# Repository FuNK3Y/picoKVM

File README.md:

# PicoKVM
An inexpensive network KVM that can switch USB and monitor inputs simultaneously

## Why
Samsung makes great monitors, but they often lack a KVM. The project started as a way to switch them along with the USB devices, over their network API. It was later generalized to most monitors, driven over HDMI DDC/CI by its own board, while still driving network-controlled monitors and devices.

## Features
- Switches the USB devices and the monitors' inputs together
- Drives most monitors over HDMI DDC/CI, and others (or any device: a lamp, ...) over the network
- No video goes through it: every computer is connected directly to every monitor, so HDCP, VRR, G-Sync, FreeSync, HDR, ... work natively
- Controlled from its button, a web page or an HTTP API, from any device on the network

## Hardware
picoKVM runs on its own board, designed in [`hardware/`](hardware/README.md): an ESP32-S3, a USB 3.0 switch (two computers, one peripheral port), two HDMI ports carrying DDC/CI only (no video) to switch monitor inputs, an RGB status LED, and a Grove port for an [M5Stack key unit](https://shop.m5stack.com/products/mechanical-key-button-unit) as the switch button.

The original build (M5Stack AtomS3 Lite + USB multiplexer) is no longer supported; its last version is [5d5997c](https://github.com/FuNK3Y/picoKVM/tree/5d5997c).

## Install
1. Open the **[browser installer](https://funk3y.github.io/picoKVM/)** in Chrome or Edge, and plug the board's AUX / FLASH USB-C port into the computer.
2. Install, then connect the board to your Wi-Fi from the same page.
3. *Visit device* opens the [settings page](#settings): set the [admin password](#admin-password) first, then the input names and the monitors.

## Wiring
- Computers' video goes directly to the monitors, as without a KVM.
- Each computer's USB goes to the board; the keyboard and mouse go to its peripheral port, through a hub (the monitor's own hub works).
- For monitors driven over DDC/CI, an HDMI cable goes from one of the board's HDMI ports to the monitor. It carries only the input-switch commands, no video. Monitors driven over the network need none.

```mermaid
graph LR
    KB["Keyboard"] <--> |USB| HUB["USB hub"]
    MOUSE["Mouse"] <--> |USB| HUB
    KVM <--> |USB| HUB
    PC1["Computer 1"] --> |Video| MON["Monitor"]
    PC2["Computer 2"] --> |Video| MON
    PC1 <--> |USB| KVM["picoKVM"]
    PC2 <--> |USB| KVM
    KVM -.-> |"HDMI (DDC/CI only)"| MON
    style MON fill:#f9f,stroke:#333
    style KVM fill:#bbf,stroke:#333
    style HUB fill:#ddd,stroke:#333
    style KB fill:#ddd,stroke:#333
    style MOUSE fill:#ddd,stroke:#333
    style PC1 fill:#ddd,stroke:#333
    style PC2 fill:#ddd,stroke:#333
```

## Settings
The settings page (*Settings*, below the switch button at `http://picokvm.local`) edits everything: Wi-Fi, input names and colors, LED brightness, admin password, monitors and [updates](#updates).

### Admin password
Once set, the admin password protects everything the settings page does: opening it, reading and changing the configuration, and installing updates, from the page or through the API. The browser asks for it (any user name); API calls send it as HTTP Basic credentials, e.g. `curl -u admin:<password>`. Switching inputs, the state and `/metrics` stay open.

**Until it is set, all of that is open to anyone on the network.**

To remove it, use *Clear password*, then *Save*, on the settings page, or send `"admin_password": null` to `/api/config`; everything above is then open again.

It travels over plain HTTP, so anyone able to watch the network traffic can read it.

### Monitors
Monitors are added on the settings page: a form for DDC/CI monitors, JSON for the others ([`config.example.json`](config.example.json) has an example of each).

#### DDC/CI monitors
Enable DDC/CI in the monitor's menu. For each computer, choose the monitor input it is on. The settings page reads the monitor: its name, the input it is on now, and the inputs it lists, named as the MCCS standard names them (VCP `0x60`: `15` DisplayPort 1, `17` HDMI 1, ...). Some monitors use other values, or name their ports differently: put the monitor on each computer's input by hand, and the page shows which value it is (*Other value...* takes any number). *Power the monitor on first* wakes up monitors that keep DDC/CI alive in standby.

The monitor must accept DDC/CI on an input that is not the active one, since it is showing the other computer when the command arrives. Most do: tested on **AOC, Samsung, Dell, Acer, Philips and Lenovo** monitors. Some have no DDC/CI at all (the Samsung G80SD): drive those over the network.

#### Samsung monitors over the network
For Samsung smart monitors without DDC/CI, the KVM sends remote-control key presses: enable IP remote on the monitor *(Connection > Network > Expert Settings)*. Find a repeatable sequence of keys that selects each input from the home screen, and write it with the [key codes](https://github.com/ollo69/ha-samsungtv-smart/blob/master/docs/Key_codes.md) as a `SamsungMonitor`. `KEY_RETURN` first also wakes the monitor up; `command_delay` (or a `delay` on one key) slows the sequence down if the menu cannot keep up.

#### Other network devices
A `GenericDevice` sends an HTTP request for each input: another monitor's API (e.g. [SmartThings](https://github.com/ollo69/ha-samsungtv-smart/issues/274#issuecomment-2597627685), untested), a lamp, ...

## Use
Switch with the button, the web page at `http://picokvm.local` (it follows the KVM whoever switches it), or the API:
```sh
curl -X POST http://picokvm.local/api/active_input/A   # or B; without the input, toggles
curl http://picokvm.local/api/active_input             # the state: active input, switching, last error
curl http://picokvm.local/api/events                   # the state as server-sent events, on every change
```
`/api/config` reads (`GET`) and writes (`POST`) the configuration, without the passwords, only `admin_password_set` tells whether one is set ([admin password](#admin-password) required). `/metrics` gives Wi-Fi signal, memory, USB power and version for Prometheus.

`picokvm` is the default hostname; it can be changed in the settings.

## Updates
*Check for updates*, then *Install*, on the settings page installs the latest [release](https://github.com/FuNK3Y/picoKVM/releases) over the network; *Upload* installs a `firmware-ota.bin` of your own. Settings are kept. The first boot of an update is a trial: if the device is not back on Wi-Fi within 2 minutes, it returns to the previous firmware.

The same through the API, with the [admin password](#admin-password):
```sh
curl -u admin:<admin_password> -X POST http://picokvm.local/api/update/latest
curl -u admin:<admin_password> --data-binary @firmware-ota.bin http://picokvm.local/api/update
```

MicroPython does not check GitHub's certificate when downloading a release: the SHA-256 GitHub publishes only guards against a corrupted download.

## ESPHome
The board can also run [ESPHome](https://esphome.io) instead of this firmware, for a native Home Assistant integration (DDC/CI monitors only). Include the [esphome/picokvm.yaml](esphome/picokvm.yaml) package, then name the computers and set the number of monitors:

```yaml
packages:
  picokvm: github://FuNK3Y/picoKVM/esphome/picokvm.yaml@main

substitutions:
  inputs:
    a: Work laptop
    b: Gaming PC
  monitors: 2
```

Each monitor's input values and the LED colors and brightness are then set from Home Assistant. [esphome/example.yaml](esphome/example.yaml) is a complete starting point; it builds, but has not been run on a board yet.

## Development
[`firmware/build.sh`](firmware/build.sh) builds MicroPython with `src/` frozen in, into `firmware/build/` (needs [ESP-IDF](https://docs.espressif.com/projects/esp-idf/en/v5.5.2/esp32s3/get-started/) v5.5.2):
```sh
. $IDF_PATH/export.sh
firmware/build.sh
```
CI runs the same build on pull requests and `main` and keeps the images as an artifact. A `v*` tag publishes a release and the [installer](install/index.html) to GitHub Pages.

The tests run the application on CPython, with stand-ins for the board ([`tests/mocks.py`](tests/mocks.py)); CI requires 95% coverage:
```sh
python3 -m unittest discover -s tests
```

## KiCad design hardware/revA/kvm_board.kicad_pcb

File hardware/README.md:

# picoKVM board — ESP32-S3 USB 3.0 KVM switch with HDMI DDC/CI

Two PCs (USB 3.0 Type-B) share one peripheral port (USB 3.0 Type-A).  An
ESP32-S3 flips the USB path and tells both monitors to change input over
HDMI DDC/CI.  The HDMI ports carry DDC/+5V only — video goes straight
from the PCs to the monitors.  The firmware is the MicroPython code in
`src/`, built into a MicroPython image by `firmware/` (see the main [README](../README.md)).

## Rev A release (ordered 2026-10-03, JLCPCB)

`revA/` holds the board exactly as it was sent to JLCPCB.  Freerouting is not
deterministic, so **`revA/kvm_board.kicad_pcb` is the design of record**: a
fresh `./build.sh` produces an equivalent board, not the same copper.

| file | what |
|---|---|
| `revA/kvm_board.kicad_pcb` / `.kicad_pro` / `.kicad_dru` | routed board (KiCad 10), its net classes and JLC design rules |
| `revA/jlcpcb/gerbers.zip`, `bom.csv`, `cpl.csv` | the files uploaded to JLCPCB (126 × 75 mm customer panel) |
| `revA/schematic_review.html` | readable schematic: every pin, its net and what else is on it |
| `revA/mechanical.txt` | connector, LED and button positions for the enclosure |
| `revA/thermal_justification.md` | proof that every single-spoke GND pad reaches the In1 plane |
| `revA/impedance.txt` | field-solver results for the 90 Ω pairs on JLC04161H-3313 |
| `revA/img/` | renders (top, bottom, iso, panel) and the Grove J8 pinout |

JLC order settings: 4 layers, 1.6 mm, **specified stackup JLC04161H-3313**,
no impedance control (accepted risk for prototypes, see below), 0.3 mm vias,
1 oz outer / 0.5 oz inner, flying-probe test, Standard PCBA top side,
**edge rails added by customer**, confirm production file and parts placement.

To regenerate the order files from the released board without re-routing:

```
mkdir -p out && cp revA/kvm_board.kicad_* out/
./build.sh fab        # panel (hw/panel.py), Gerbers, PTH/NPTH drill, BOM, CPL -> out/jlcpcb/
```

## Build

```
./build.sh          # netlist + ERC, PCB, routing, DRC, renders, JLCPCB files (all in Docker)
./build.sh noroute  # same, stopping at the placed, unrouted board
./build.sh parts    # re-import the LCSC symbols/footprints/3D models
./build.sh shell    # shell inside the toolchain (KiCad 10 + SKiDL + easyeda2kicad)
```

Sources:

| file | what |
|---|---|
| `hw/kvm_board.py` | the schematic, as SKiDL code — edit this, not the netlist |
| `hw/make_pcb.py` | builds the 4-layer `.kicad_pcb`: placement, planes, net classes, JLC rules |
| `hw/route_ss.py` | hand-designed USB 3.0 SuperSpeed pairs (coupled, matched, no vias) |
| `hw/route_usb2.py` | hand-designed USB 2.0 pairs (coupled, matched, symmetric via pairs) |
| `hw/finish.py` | power neck-downs + plane fanout before routing; GND stitching after |
| `hw/route.py` | Freerouting round-trip (Specctra DSN/SES) for everything else |
| `hw/impedance.py` | 2-D field solver for the 90 Ω pairs on the JLC 3313 stackup |
| `hw/make_fab.py` | JLCPCB `bom.csv` / `cpl.csv` (CPL expressed in JLC's own footprint frame) |
| `hw/panel.py` | JLC assembly panel: rails, mouse bites, fiducials, tooling holes |
| `hw/thermal_report.py` | proves every single-spoke GND pad reaches the In1 plane |
| `hw/checks.py` | manufacturing checks beyond DRC, tuned to JLCDFM: vias near pads, SMD near through-hole pads, tracks near mask openings, USB 2 skew (`./build.sh checks`; part of every build) |
| `hw/review.py` | generates `schematic_review.html` |
| `hw/jlcref.py` | fetches JLC's footprints into `hw/lib/jlcref/` (used by `make_fab.py`) |
| `hw/lib/` | LCSC/EasyEDA imports; only the 3D models the board uses are committed (`./build.sh parts` re-fetches the rest, incl. STEP) |

Outputs in `out/`: `kvm_board.kicad_pro/.kicad_pcb` (open in KiCad 10),
`kvm_board.net`, `kvm_board.erc`, `drc.rpt`, `img/`, `jlcpcb/`,
`mechanical.txt` (positions for the case) and **`schematic_review.html`** —
the reviewable schematic: every chip and connector pin with its net and what
else is on it, grouped by function, plus a net index and automatic checks.

## Status

- [x] Circuit complete, ERC clean (0 errors / 0 warnings); D3 pin 3 (DOUT) is
      explicitly marked no-connect (single LED, no chain)
- [x] All parts in JLCPCB/LCSC stock (checked 2026-10-01); passives are basic parts
- [x] Placed and **fully routed**: DRC 0 errors, 0 unconnected.  Board:
      `out/drc.rpt`; JLC panel: `out/drc_panel.rpt`.  `min_resolved_spokes`
      is 1; every pad that would have a single outer-pour spoke is proven to
      reach the In1 GND plane independently in `out/thermal_justification.md`
- [x] 90 Ω pair geometry verified with a 2-D field solver (`hw/impedance.py`, see below)
- [ ] Human review of `out/schematic_review.html` (the schematic is code)
- [ ] Human review of the autorouted part in KiCad (DRC-clean and fully
      connected; not yet reviewed by eye)
- [x] Ordered from JLCPCB (5 assembled boards, rev A), files in `revA/`
- [ ] JLC production file and placement preview approved
- [ ] Prototype bring-up per the test plan below; DDC/CI with your monitors

`lib_footprint_issues` in `drc.rpt` only appears in the headless container
(no global library table) and can be ignored.  `lib_footprint_mismatch` on D3 is
intentional: the build replaces that EasyEDA footprint's open courtyard with a
closed rectangle and corrects its 3D-model offset (`hw/make_pcb.py`
`FIX_COURTYARD`, model offset in `hw/lib/lcsc.pretty`); its pads, numbering,
mask and paste are unchanged, and JLC's SMT check (its own C5378721 model on
our pads via the CPL) reports no pin-edge finding for D3.

### Toolchain

All versions are pinned (Dockerfile / `build.sh`): KiCad 10.0.6
(`kicad/kicad:10.0.6-full`), SKiDL 2.3.0, easyeda2kicad 1.0.1,
Freerouting 2.4.1 on `eclipse-temurin:25.0.4.1_1-jre`.

KiCad's Python bindings occasionally segfault in standalone scripts — on
both 9.0.9 and 10.0.6, mostly around zone filling.  Every script saves only
when its work is done and leaves via `os._exit(0)`, and `build.sh` retries
a crashed step (you'll see "crashed, retrying" in the log).  Routing results
vary slightly from run to run because Freerouting is not deterministic.

## How the board is routed

1. **USB 3.0 SuperSpeed** (`route_ss.py`): six pairs routed deliberately on
   F.Cu over the In1 GND plane — coupled 0.15/0.15 mm, 45° corners in
   cancelling pairs, intra-pair skew ≤ 0.1 mm, no vias, straight through
   the flow-through ESD parts.  Locked.
2. **USB 2.0** (`route_usb2.py`): the three switched pairs (USB A, USB B,
   peripheral) routed the same way — coupled 0.15/0.15 mm from connector to
   switch, D+/D− skew 0.000 mm (a 0.6 mm trombone on the peripheral pair
   cancels its one unbalanced 90° turn), symmetric via pairs where a pair
   changes layer (USB A: 0 vias, USB B: 4, peripheral: 6, i.e. 3 symmetric
   pairs; the B.Cu sections reference In2 (+3V3), the F.Cu ones In1 (GND)), straight through
   flow-through TPD4E05U06 ESD parts.  The TS3USB221A switch keeps each
   pair on adjacent pins, so pairs only separate for the last 0.1 mm into
   0.5 mm-pitch pads.  Locked.
3. **Pre-route** (`finish.py fanout`): every GND / +3V3 SMD pad gets a stub +
   via into its plane (In1 = GND, In2 = +3V3); fine-pitch power pins get
   neck-down stubs.  Locked.
4. **Everything else** (`route.py` + Freerouting 2.4.1 on Java 25):
   power, I²C, GPIO, aux USB-C (Full Speed only) on F.Cu/B.Cu.
5. **Stitching** (`finish.py stitch`): GND vias on a 4 mm grid tie the F/B
   pours to In1.

## Stackup and impedance

- **JLC04161H-3313**: L1 signal, L2 GND, L3 +3V3, L4 signal.  Select this
  stackup when ordering.  USB pairs on L4 (B.Cu) reference the L3 +3V3
  plane, AC-coupled to GND by the decoupling capacitors.
- Net class `USB_DIFF`: 0.15 mm track / 0.15 mm gap.  Verified with
  `hw/impedance.py`, a 2-D quasi-static field solver of the cross-section
  using JLC's published 3313 data (prepreg 0.0994 mm, Dk 4.1; solder mask
  1.2/0.6 mil, Dk 3.8; trapezoid etch W−0.025 mm; 0.04 mm finished copper).
  The solver matches Hammerstad-Jensen within 1.1–1.6 % on single
  microstrips.  Result (`out/impedance.txt`):
  - **Zdiff ≈ 90 Ω** with solder mask (99 Ω without), converging to ~89–90 Ω
  - every tolerance corner (Dk ±0.2, prepreg ±10 %, heavier etch, thinner
    copper, W or S ±0.02 mm) stays within **86–94 Ω**
- **Rev A is ordered without impedance control** (+$33): an accepted risk
  for 5 prototypes.  The stackup is specified, so the geometry gives the
  calculated ~90 Ω, but it is not measured or guaranteed by the fab; USB 3
  is validated on the prototypes.  For production, order impedance control,
  90 Ω differential on L1 referenced to L2.  JLC's own calculator (web only) is
  the final word; this is the same class of computation.
- ESP32 antenna: flush with the right edge, with a copper keep-out rule area
  under it on all four layers (no tracks, vias, pads or plane fill), extending
  2.5 mm past the module's sides.  Freerouting and the fanout/stitching steps
  respect it.

## Design decisions

- **No AC-coupling caps on the SuperSpeed lines.**  The PC and the device
  already AC-couple their transmitters, and the HD3SS3212 must be DC-biased
  from one side (datasheet SLASE74F §10.1).  Caps on the board would leave
  the switch floating.
- **TX/RX crossover:** PC SSRX (B pins 8/9) ↔ peripheral SSTX (A pins 8/9),
  PC SSTX (B 5/6) ↔ peripheral SSRX (A 5/6), via mux channels 0/1.
- **LM66100 CE is tied to VOUT**, not GND — that is what enables its
  reverse-current blocking, so USB A can't back-feed USB B.
- **TS3USB221A** (µQFN-10) as the USB 2.0 switch: unlike the TS3USB30E, its
  D+/D− pins are adjacent for every port, so the pairs stay coupled up to the
  pins.  S = L selects port 1 (USB A), same polarity as the HD3SS3212 and
  TPS2116, so one `USB_SEL` still drives all three.
- **USB 2.0 ESD**: TPD4E05U06 (the SuperSpeed ESD part, channel 1 only) in
  flow-through right after J1 and J2 and on the switch's common side, instead
  of USBLC6s off to the side: no stubs, 0.5 mm pitch.
- **HDMI +5V** (pin 18; HDMI asks 4.8–5.3 V): LM66100 ideal diode (~5 mV
  drop, blocks back-feed from the monitor) + 100 mA PTC.  Expect ~4.9 V from
  a 5.0 V PC port, ~4.5 V in the worst case (4.75 V port and a heavily
  loaded cable) — check on the prototype.
- **No added vias inside exposed pads**: the HD3SS3212's thermal pad joins
  its GND pins, which take vias outside the chip (no solder wicking, no
  filled vias needed).  The one exception is the ESP32-S3 module's own
  footprint (Espressif's land pattern), which has 0.3 mm thermal vias in its
  centre GND pad by design.
- Peripheral VBUS: the TPS2116 picks the source and follows `USB_SEL`
  (its PR1 pin), so power always comes from the PC whose data is selected.
  A TPS2553 after it switches the port on/off and limits it to 1.2–1.38 A
  (R_ILIM 20 kΩ) with a fault flag — one GPIO each, no pin combinations to
  get wrong.  The board itself is powered by whichever of USB A / USB B / AUX
  is present.

## Decoupling (per TI datasheets)

- U4 TPS2116: 1 µF on each VIN at the IC (C4 VBUS_A, C5 VBUS_B; datasheet
  9.2 / 10.1); C6 100 nF on VOUT (≥ 0.1 µF for soft start, 7.3.2), which is
  also U20's input capacitor (TPS2553: 0.1 µF next to IN).
- U6 / U7 LM66100: 1 µF on each VIN (C23, C24) and 10 µF on +5V_SYS between
  them (C25), datasheet 10.2 / 11.1.  U8 (AUX) has C10 / C11 beside it.
- Peripheral port after U20: 2 × 22 µF + 100 nF at J3.

## Prototype test plan (rev A)

USB host ports are specified for 0.9 A (USB 3) but their actual trip point
is not a design limit, so rev A is validated inside this envelope:

- **Base envelope:** nothing connected to J7/J9; HDMI +5 V, Grove and LEDs
  count in the measured board current.  Assume one PC port supplies both the
  board and the peripheral (the AUX input does not guarantee a favourable
  split).
- **Peripheral current:** 0.5 A minus whatever the measured board current
  exceeds 0.35 A, on a USB 3 host port (0.9 A budget); higher loads, and the
  test at the U20 limit (1.2–1.38 A), only from a source known to supply
  them (bench supply or powered hub).
- **Measure:** source VBUS, VBUS at J3 and the drop between them, at 0.5 A
  and (on a capable source) at the U20 limit — judge J3 against what the
  peripheral needs, not a fixed number; temperature of U4, U20 and the VBUS
  tracks with a thermal camera or thermocouple after 10 min at load.
- **Switchover:** scope +5V_SYS and VBUS_PERIPH while toggling USB_SEL with a
  load on J3.
- **Inrush at plug-in:** +5V_SYS carries ~21 µF (C11, C12, C25) charged
  through U6/U7/U8 with no current limit; scope VBUS at plug-in on A, B and
  AUX separately, and plug them one after another, on a protected source.
- **U5 AP2112K:** temperature with Wi-Fi active continuously (expected
  ~0.1 A average, ~0.17 W).
- **Grove short:** short GROVE_5V to GND; F4 (100 mA PTC) trips in seconds,
  not instantly — check that +5V_SYS and the ESP32 stay up, and that F4
  recovers.
- **HDMI +5 V:** voltage at J5/J6 pin 18 with each monitor (spec 4.8–5.3 V).
- **USB 3 / USB 2:** throughput with a real SuperSpeed device and a
  High-Speed device on each PC; DDC/CI with each monitor.

## Firmware contract

Implemented by the firmware in `src/` (`src/board.py` holds these pins).

| GPIO | function |
|---|---|
| 1 / 2 | HDMI 1 DDC SDA / SCL (I2C0) |
| 4 / 5 | HDMI 2 DDC SDA / SCL (I2C1) |
| 6 / 7 | spare (not broken out; HDMI hot-plug detect is deliberately not wired: DDC/CI needs only SDA/SCL + 5 V, and a monitor can be found by probing I2C 0x50) |
| 8 | `USB_SEL` — low = USB A, high = USB B: USB 3 + USB 2 data **and** peripheral power source |
| 9 | `USB_OE_N` — low = data muxes on (pulled up: off at reset) |
| 10 | `PERIPH_EN` — high = peripheral power on (pulled down: off at reset) |
| 16 | `PERIPH_FAULT_N` — input, low = peripheral over-current / over-temperature |
| 11 / 12 | USB A / USB B VBUS present (10k/15k divider: 5 V → 3.0 V, max 3.3 V at an out-of-spec 5.5 V) |
| 13 | PC-switch button, active low: on-board SW3 **and** Grove J8 key, M5 white wire |
| 14 | on-board status LED data (SK6812 RGB, GRB order, 800 kHz) — set the colour per selected PC |
| 15 | spare (not broken out) |
| 19 / 20 | native USB (aux USB-C) |
| 17 | remote button RGB LED data (SK6812), Grove J8 LED, M5 yellow wire |
| 43 / 44 | UART0 on J7 (GND, TX, RX, 3V3) |
| 18, 21, 35–42, 47, 48 | spare, on J9 |

### Connectors for the box

- **J8 — Grove (HY2.0-4P), left edge, centred — M5Stack pinout:**
  looking into the socket from outside, latch window on top, left to right:
  GND, **5 V** (via 100 mA PTC), LED data (GPIO17, SK6812/NeoPixel), key
  (GPIO13, active low, 10k pull-up on board).  On an M5Stack cable that is
  black, red, yellow, white -- verified against a real Unit Key.  (The
  footprint's pad 1 is GND; Seeed cables use other colours.)
  100 Ω series resistors on both signals.  Made for the M5Stack Unit Key
  (mechanical key + RGB LED): it plugs straight in.  Avoid Seeed Grove
  modules that pull their signal up to VCC — they would put 5 V on an ESP32
  pin.
- **J9 — 2×8 header, 2.54 mm (assembled, C68234):**

  Even pins are the row nearest the ESP32, in module-pin order, so the
  fan-out is straight:

  | pin | signal | pin | signal |
  |---|---|---|---|
  | 1 | GPIO48 | 2 | GPIO35 |
  | 3 | GPIO47 | 4 | GPIO36 |
  | 5 | GPIO21 | 6 | GPIO37 |
  | 7 | GPIO18 | 8 | GPIO38 |
  | 9 | GND | 10 | GPIO39 |
  | 11 | 3V3 | 12 | GPIO40 |
  | 13 | 5V (5V_SYS) | 14 | GPIO41 |
  | 15 | GND | 16 | GPIO42 |

  The module is the **N8R2** (8 MB flash, 2 MB quad PSRAM).  GPIO35–37 are
  free only because its PSRAM is quad SPI — don't substitute an octal-PSRAM
  module (N8R8, N16R8…), which uses those pins internally.  The firmware is
  built on MicroPython's plain ESP32_GENERIC_S3 configuration: it detects the quad PSRAM at boot (the
  `SPIRAM_OCT` variant is for octal PSRAM and won't start it).  GPIO39–42 are also the JTAG pins (usable as
  normal GPIO; JTAG is over USB on the S3).  The 5V pin is the board's
  internal rail (ideal-diode OR of the USB inputs) — keep loads small.
- **J7 — UART header (assembled, C32713270):** GND, TX, RX, 3V3.

### Mechanical (for the enclosure)

- Board 112 × 75 mm, plain rectangle; the edge connectors protrude past it by
  up to 1.5 mm (see `out/mechanical.txt`).  The ESP32
  antenna is at the right edge, y 31–49: keep metal, screws and conductive
  filament ≥ 5 mm away from it; plain PLA/PETG walls are fine.
- Four M3 holes, 4 mm in from each corner; nothing within Ø8 mm of them.
- Edge connectors stick out up to 1.5 mm (2 mm wall − 0.5 mm); see
  `out/mechanical.txt` for each connector's edge, position and protrusion.
- Rear edge (PC side): USB A and USB B inputs (USB 3.0 Type-B), aux/flash (USB-C).
- Front edge (desk side): peripherals (USB-A), HDMI 1, HDMI 2, and the
  side-emitting RGB status LED (SK6812SIDE-A, lens 4 x 2 mm, centre 1 mm
  above the board), which shines straight out of the edge: a ~2 mm hole or
  light pipe in the wall is all it needs.  Its VDD comes from +5V_SYS through
  a 1N4148W (~4.3 V) so the 3.3 V data line clears VIH = 0.65 x VDD.
- Left edge: Grove button port, centred.  Right edge: ESP32 antenna.
- Buttons are 3 mm tall (TS-1187A-C-F-B): press them through flexures in the
  lid.  Positions in `out/mechanical.txt`.
- Inboard, rear: GPIO header J9, UART header J7, RESET / BOOT / PC-switch
  buttons (bench use; the Grove port is the user's button).

Switch sequence (every step is a single GPIO write):

1. `PERIPH_EN` = 0 — peripherals off
2. `USB_SEL` = target PC — data and power source follow together
3. wait ~200 ms — devices see a clean disconnect
4. `PERIPH_EN` = 1 — peripherals power up on the new PC and enumerate
5. send DDC/CI "input source" (VCP 0x60) to both monitors

MicroPython, e.g.:

```python
en.off(); sel.value(1); time.sleep_ms(200); en.on()   # switch to USB B
```

**Caveat:** many monitors only accept DDC/CI on the input currently being
shown.  Test your monitors with an ESP32 dev board + HDMI breakout before
ordering.

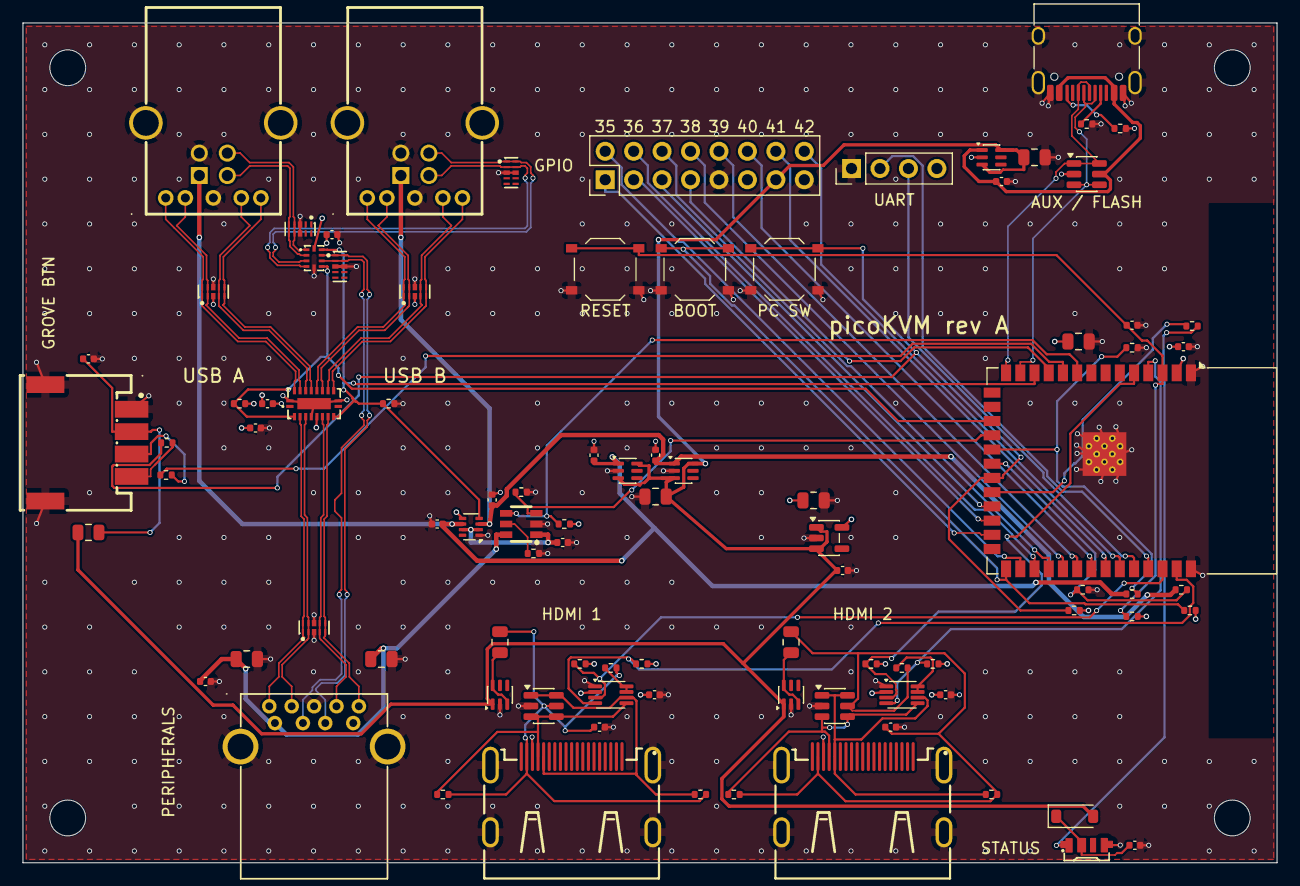
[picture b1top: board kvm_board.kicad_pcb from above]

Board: 4 copper layers, 112.0 x 75.0 mm, 95 parts (0 on the bottom side), 75 nets.

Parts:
C1, C3, C6, C9, C14, C15, C16, C17, C19, C21, C22: 100nF; C_0402_1005Metric
C2, C4, C5, C10, C12, C20, C23, C24: 1uF; C_0402_1005Metric
C7, C8, C18: 22uF; C_0805_2012Metric
C11, C13, C25: 10uF; C_0805_2012Metric
D3: SK6812SIDE-A; LED-SMD_4P-L4.0-W1.6-L
D4: 1N4148W; D_SOD-123
F2, F3, F4: 100mA; Fuse_0805_2012Metric
H1, H2, H3, H4: MountingHole; MountingHole_3.2mm_M3
J1, J2: HC-USB3.0-L1845-BF; USB-B-TH_9P-L18.5-W12.0
J3: HC-USB3.0-L168-WP; USB-TH_USB3.0-A
J4: USB_C_Receptacle_USB2.0_16P; USB_C_Receptacle_HRO_TYPE-C-31-M-12
J5, J6: HDMI-001; HDMI-SMD_19P-P0.50-H-F
J7: UART; PinHeader_1x04_P2.54mm_Vertical
J8: GROVE_BTN; CONN-SMD_4P-P2.00_ZX-HY2.0-4PWT
J9: GPIO; PinHeader_2x08_P2.54mm_Vertical
R1, R2: 5.1k; R_0402_1005Metric
R3, R4, R6, R7, R8, R10, R22, R23, R24: 10k; R_0402_1005Metric
R5: 20k; R_0402_1005Metric
R9, R11: 15k; R_0402_1005Metric
R12, R17: 200k; R_0402_1005Metric
R13, R14, R18, R19: 4.7k; R_0402_1005Metric
R15, R16, R20, R21: 2k; R_0402_1005Metric
R25, R26, R27: 100; R_0402_1005Metric
SW1: RESET; SW_Push_1P1T_XKB_TS-1187A
SW2: BOOT; SW_Push_1P1T_XKB_TS-1187A
SW3: SWITCH; SW_Push_1P1T_XKB_TS-1187A
U1: ESP32-S3-WROOM-1-N8R2; ESP32-S3-WROOM-1
U2: HD3SS3212IRKSR; DHVQFN-20_L4.5-W2.5-P0.50-BL-EP
U3: TS3USB221ARSER; UQFN-10_L2.0-W1.5-P0.50-BL
U4: TPS2116DRL; SOT-583-8
U5: AP2112K-3.3; SOT-23-5
U6, U7, U8, U21, U22: LM66100DCK; SOT-363_SC-70-6
U9, U10: PCA9306DC; VSSOP-8_2.3x2mm_P0.5mm
U11, U12, U13, U17, U18, U19: TPD4E05U06DQAR_C138714; USON-10_L2.5-W1.0-P0.50-BL
U14, U15, U16: USBLC6-2SC6; SOT-23-6
U20: TPS2553DBVR; SOT-23-6_L2.9-W1.6-P0.95-LS2.8-BR

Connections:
+3V3: C1.1, C2.1, C3.1, C13.1, C15.1, C17.1, C18.1, C19.1, J7.4, J9.11, R4.2, R7.2, R13.2, R14.2, R18.2, R19.2, R22.2, R23.2, R24.2, U1.2, U2.6, U3.10, U4.5, U5.5, U9.2, U10.2
+5V_SYS: C11.1, C12.1, C25.1, D4.2, F4.1, J9.13, U5.1, U5.3, U6.3, U6.6, U7.3, U7.6, U8.3, U8.6, U21.1, U22.1
AUX_CC1: J4.A5, R1.1
AUX_CC2: J4.B5, R2.1
AUX_DN: J4.A7, J4.B7, U1.13, U14.3, U14.4
AUX_DP: J4.A6, J4.B6, U1.14, U14.1, U14.6
BOOT: R23.1, SW2.1, U1.27
BTN_SWITCH: R24.1, R26.1, SW3.1, U1.21
DDC1_SCL: R13.1, U1.38, U9.3
DDC1_SDA: R14.1, U1.39, U9.4
DDC1_VREF2: R12.1, U9.7, U9.8
DDC2_SCL: R18.1, U1.5, U10.3
DDC2_SDA: R19.1, U1.4, U10.4
DDC2_VREF2: R17.1, U10.7, U10.8
EN: C20.1, R22.1, SW1.1, U1.3
EXT_LED: R27.1, U1.10
GND: C1.2, C2.2, C3.2, C4.2, C5.2, C6.2, C7.2, C8.2, C9.2, C10.2, C11.2, C12.2, C13.2, C14.2, C15.2, C16.2, C17.2, C18.2, C19.2, C20.2, C21.2, C22.2, C23.2, C24.2, C25.2, D3.4, J1.4, J1.7, J1.10, J1.11, J2.4, J2.7, J2.10, J2.11, J3.4, J3.7, J3.10, J4.A1, J4.A12, J4.B1, J4.B12, J4.SH, J5.17, J5.20, J5.21, J5.22, J5.23, J6.17, J6.20, J6.21, J6.22, J6.23, J7.1, J8.1, J8.5, J8.6, J9.9, J9.15, R1.2, R2.2, R3.2, R5.2, R6.2, R9.2, R11.2, SW1.2, SW2.2, SW3.2, U1.1, U1.40, U1.41, U2.5, U2.11, U2.20, U2.21, U3.5, U4.1, U5.2, U6.2, U7.2, U8.2, U9.1, U10.1, U11.3, U11.8, U12.3, U12.8, U13.3, U13.8, U14.2, U15.2, U16.2, U17.3, U17.8, U18.3, U18.8, U19.3, U19.8, U20.2, U21.2, U22.2
GPIO18: J9.7, U1.11
GPIO21: J9.5, U1.23
GPIO35: J9.2, U1.28
GPIO36: J9.4, U1.29
GPIO37: J9.6, U1.30
GPIO38: J9.8, U1.31
GPIO39: J9.10, U1.32
GPIO40: J9.12, U1.33
GPIO41: J9.14, U1.34
GPIO42: J9.16, U1.35
GPIO47: J9.3, U1.24
GPIO48: J9.1, U1.25
GROVE_5V: C22.1, F4.2, J8.2
GROVE_BTN: J8.4, R26.2
GROVE_LED: J8.3, R27.2
HDMI1_5V: C14.1, F2.2, J5.18, R12.2, R15.2, R16.2, U15.5
HDMI1_5V_D: F2.1, U21.3, U21.6
HDMI1_SCL: J5.15, R15.1, U9.6, U15.1, U15.6
HDMI1_SDA: J5.16, R16.1, U9.5, U15.3, U15.4
HDMI2_5V: C16.1, F3.2, J6.18, R17.2, R20.2, R21.2, U16.5
HDMI2_5V_D: F3.1, U22.3, U22.6
HDMI2_SCL: J6.15, R20.1, U10.6, U16.1, U16.6
HDMI2_SDA: J6.16, R21.1, U10.5, U16.3, U16.4
LED_DIN: D3.1, R25.2
LED_RGB: R25.1, U1.22
LED_VDD: C21.1, D3.2, D4.1
PCA_DN: J1.2, U3.2, U11.5, U11.6
PCA_DP: J1.3, U3.1, U11.4, U11.7
PCA_SSRX_N: J1.8, U2.18, U17.2, U17.9
PCA_SSRX_P: J1.9, U2.19, U17.1, U17.10
PCA_SSTX_N: J1.5, U2.16, U17.5, U17.6
PCA_SSTX_P: J1.6, U2.17, U17.4, U17.7
PCB_DN: J2.2, U3.4, U12.2, U12.9
PCB_DP: J2.3, U3.3, U12.1, U12.10
PCB_SSRX_N: J2.8, U2.14, U18.2, U18.9
PCB_SSRX_P: J2.9, U2.15, U18.1, U18.10
PCB_SSTX_N: J2.5, U2.12, U18.5, U18.6
PCB_SSTX_P: J2.6, U2.13, U18.4, U18.7
PERIPH_EN: R6.1, U1.18, U20.3
PERIPH_FAULT_N: R7.1, U1.9, U20.4
PERIPH_ILIM: R5.1, U20.5
PER_DN: J3.2, U3.7, U13.2, U13.9
PER_DP: J3.3, U3.8, U13.1, U13.10
PER_SSRX_N: J3.5, U2.8, U19.5, U19.6
PER_SSRX_P: J3.6, U2.7, U19.4, U19.7
PER_SSTX_N: J3.8, U2.4, U19.2, U19.9
PER_SSTX_P: J3.9, U2.3, U19.1, U19.10
RXD0: J7.3, U1.36
TXD0: J7.2, U1.37
USB_OE_N: R4.1, U1.17, U2.2, U3.6
USB_SEL: R3.1, U1.12, U2.9, U3.9, U4.4
VBUS_A: C4.1, C23.1, J1.1, R8.1, U4.6, U6.1
VBUS_AUX: C10.1, J4.A4, J4.A9, J4.B4, J4.B9, U8.1, U14.5
VBUS_A_SENSE: R8.2, R9.1, U1.19
VBUS_B: C5.1, C24.1, J2.1, R10.1, U4.3, U7.1
VBUS_B_SENSE: R10.2, R11.1, U1.20
VBUS_PERIPH: C7.1, C8.1, C9.1, J3.1, U20.6
VBUS_PERIPH_RAW: C6.1, U4.2, U4.7, U20.1

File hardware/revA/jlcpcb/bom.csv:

Comment,Designator,Footprint,LCSC Part #
100nF,"C1,C3,C6,C9,C14,C15,C16,C17,C19,C21,C22",C_0402_1005Metric,C1525
1uF,"C2,C4,C5,C10,C12,C20,C23,C24",C_0402_1005Metric,C52923
22uF,"C7,C8,C18",C_0805_2012Metric,C45783
10uF,"C11,C13,C25",C_0805_2012Metric,C15850
SK6812SIDE-A,D3,LED-SMD_4P-L4.0-W1.6-L,C5378721
1N4148W,D4,D_SOD-123,C81598
100mA,"F2,F3,F4",Fuse_0805_2012Metric,C20975
HC-USB3.0-L1845-BF,"J1,J2",USB-B-TH_9P-L18.5-W12.0,C7501849
HC-USB3.0-L168-WP,J3,USB-TH_USB3.0-A,C7501850
USB_C_Receptacle_USB2.0_16P,J4,USB_C_Receptacle_HRO_TYPE-C-31-M-12,C165948
HDMI-001,"J5,J6",HDMI-SMD_19P-P0.50-H-F,C138388
UART,J7,PinHeader_1x04_P2.54mm_Vertical,C32713270
GROVE_BTN,J8,CONN-SMD_4P-P2.00_ZX-HY2.0-4PWT,C7429571
GPIO,J9,PinHeader_2x08_P2.54mm_Vertical,C68234
5.1k,"R1,R2",R_0402_1005Metric,C25905
10k,"R3,R4,R6,R7,R8,R10,R22,R23,R24",R_0402_1005Metric,C25744
20k,R5,R_0402_1005Metric,C25765
15k,"R9,R11",R_0402_1005Metric,C25756
200k,"R12,R17",R_0402_1005Metric,C25764
4.7k,"R13,R14,R18,R19",R_0402_1005Metric,C25900
2k,"R15,R16,R20,R21",R_0402_1005Metric,C4109
100,"R25,R26,R27",R_0402_1005Metric,C25076
BOOT/RESET/SWITCH,"SW1,SW2,SW3",SW_Push_1P1T_XKB_TS-1187A,C571338
ESP32-S3-WROOM-1-N8R2,U1,ESP32-S3-WROOM-1,C2913204
HD3SS3212IRKSR,U2,DHVQFN-20_L4.5-W2.5-P0.50-BL-EP,C544517
TS3USB221ARSER,U3,UQFN-10_L2.0-W1.5-P0.50-BL,C128396
TPS2116DRL,U4,SOT-583-8,C3235557
AP2112K-3.3,U5,SOT-23-5,C51118
LM66100DCK,"U6,U7,U8,U21,U22",SOT-363_SC-70-6,C2869734
PCA9306DC,"U9,U10",VSSOP-8_2.3x2mm_P0.5mm,C33196
TPD4E05U06DQAR_C138714,"U11,U12,U13,U17,U18,U19",USON-10_L2.5-W1.0-P0.50-BL,C138714
USBLC6-2SC6,"U14,U15,U16",SOT-23-6,C7519
TPS2553DBVR,U20,SOT-23-6_L2.9-W1.6-P0.95-LS2.8-BR,C55266

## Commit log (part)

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2025-02-07 Tentative devContainer
2025-02-07 Update devcontainer.json
    With a full python
2025-02-07 Linting
2025-02-07 Increase line length
2025-02-07 Read first response from WS before sending anything
2025-02-08 Fix power_on
2025-02-08 Fix linting
2025-02-08 Run set_input in parallel
2025-02-08 Sample config file
2025-02-08 Readme & fix command_delay
2025-02-08 Fix channel_uri
2025-02-08 Fix token aquisition flow
2025-02-08 Some mermaid
2025-02-08 Improve readme
2025-02-08 Update README.md
    Fix typo
2025-02-08 Typo
2025-02-08 Simplify JS
2025-02-09 Add blinking led, rename set_active_input
2025-02-09 Implement locking
2025-02-09 Fix order
2025-02-11 Move handle_client to webserver
2025-02-24 Add physical button mgmt
2025-02-24 Fix racing condition that led to the LED remaining on
2025-02-25 Properly cancel the blinking if case of exception
2025-02-28 Fix initial irq trigger on boot
2025-02-28 Introduce per-command delay
2025-02-28 Let readme reflect new config
2025-02-28 Fix typo
2025-02-28 Fix typos
2025-04-21 Switch from interupt to polling not to mess with asyncio
2025-04-21 Stop catching unnecessary exceptions
2025-04-21 Remove space
2025-04-22 Remove powerstate check as using KEY_POWER is not mandary for wake up Update readme & config accordingly
2025-04-22 Add timeout
2025-06-01 - Disable wifi power mgmt. - Rename set_active_input and get_active_input to active_input to be more REST
2025-06-01 Reuse aiohttp over different call.
2025-06-01 Revert "Reuse aiohttp over different call."
    This reverts commit b5aa8036a9db4efd8c93f0e05cf689e5125a7603.
2025-06-04 Add repeat in command dict
2025-06-04 Garbage collect
2025-06-06 Improve wifi reconnection
2025-06-06 Use constant for powersave, harmonize private attribute naming
2025-06-08 Add some debug
2025-06-14 Migration to Atom + minor improvements
2025-06-14 Fix sample config nesting
2025-06-15 Add some explicit garbage collecting to fight error 12
2025-06-20 Remove mdns lib as builtin feature is working
2025-06-20 Cleanup
2025-07-10 Static sslContext to save up on memory
2025-07-11 Fix naming
2025-07-12 Add metrics
2025-07-14 Change gc invocation strategy
2025-07-14 Add mcu temperature
2026-01-19 Fix API URL formatting in README.md
